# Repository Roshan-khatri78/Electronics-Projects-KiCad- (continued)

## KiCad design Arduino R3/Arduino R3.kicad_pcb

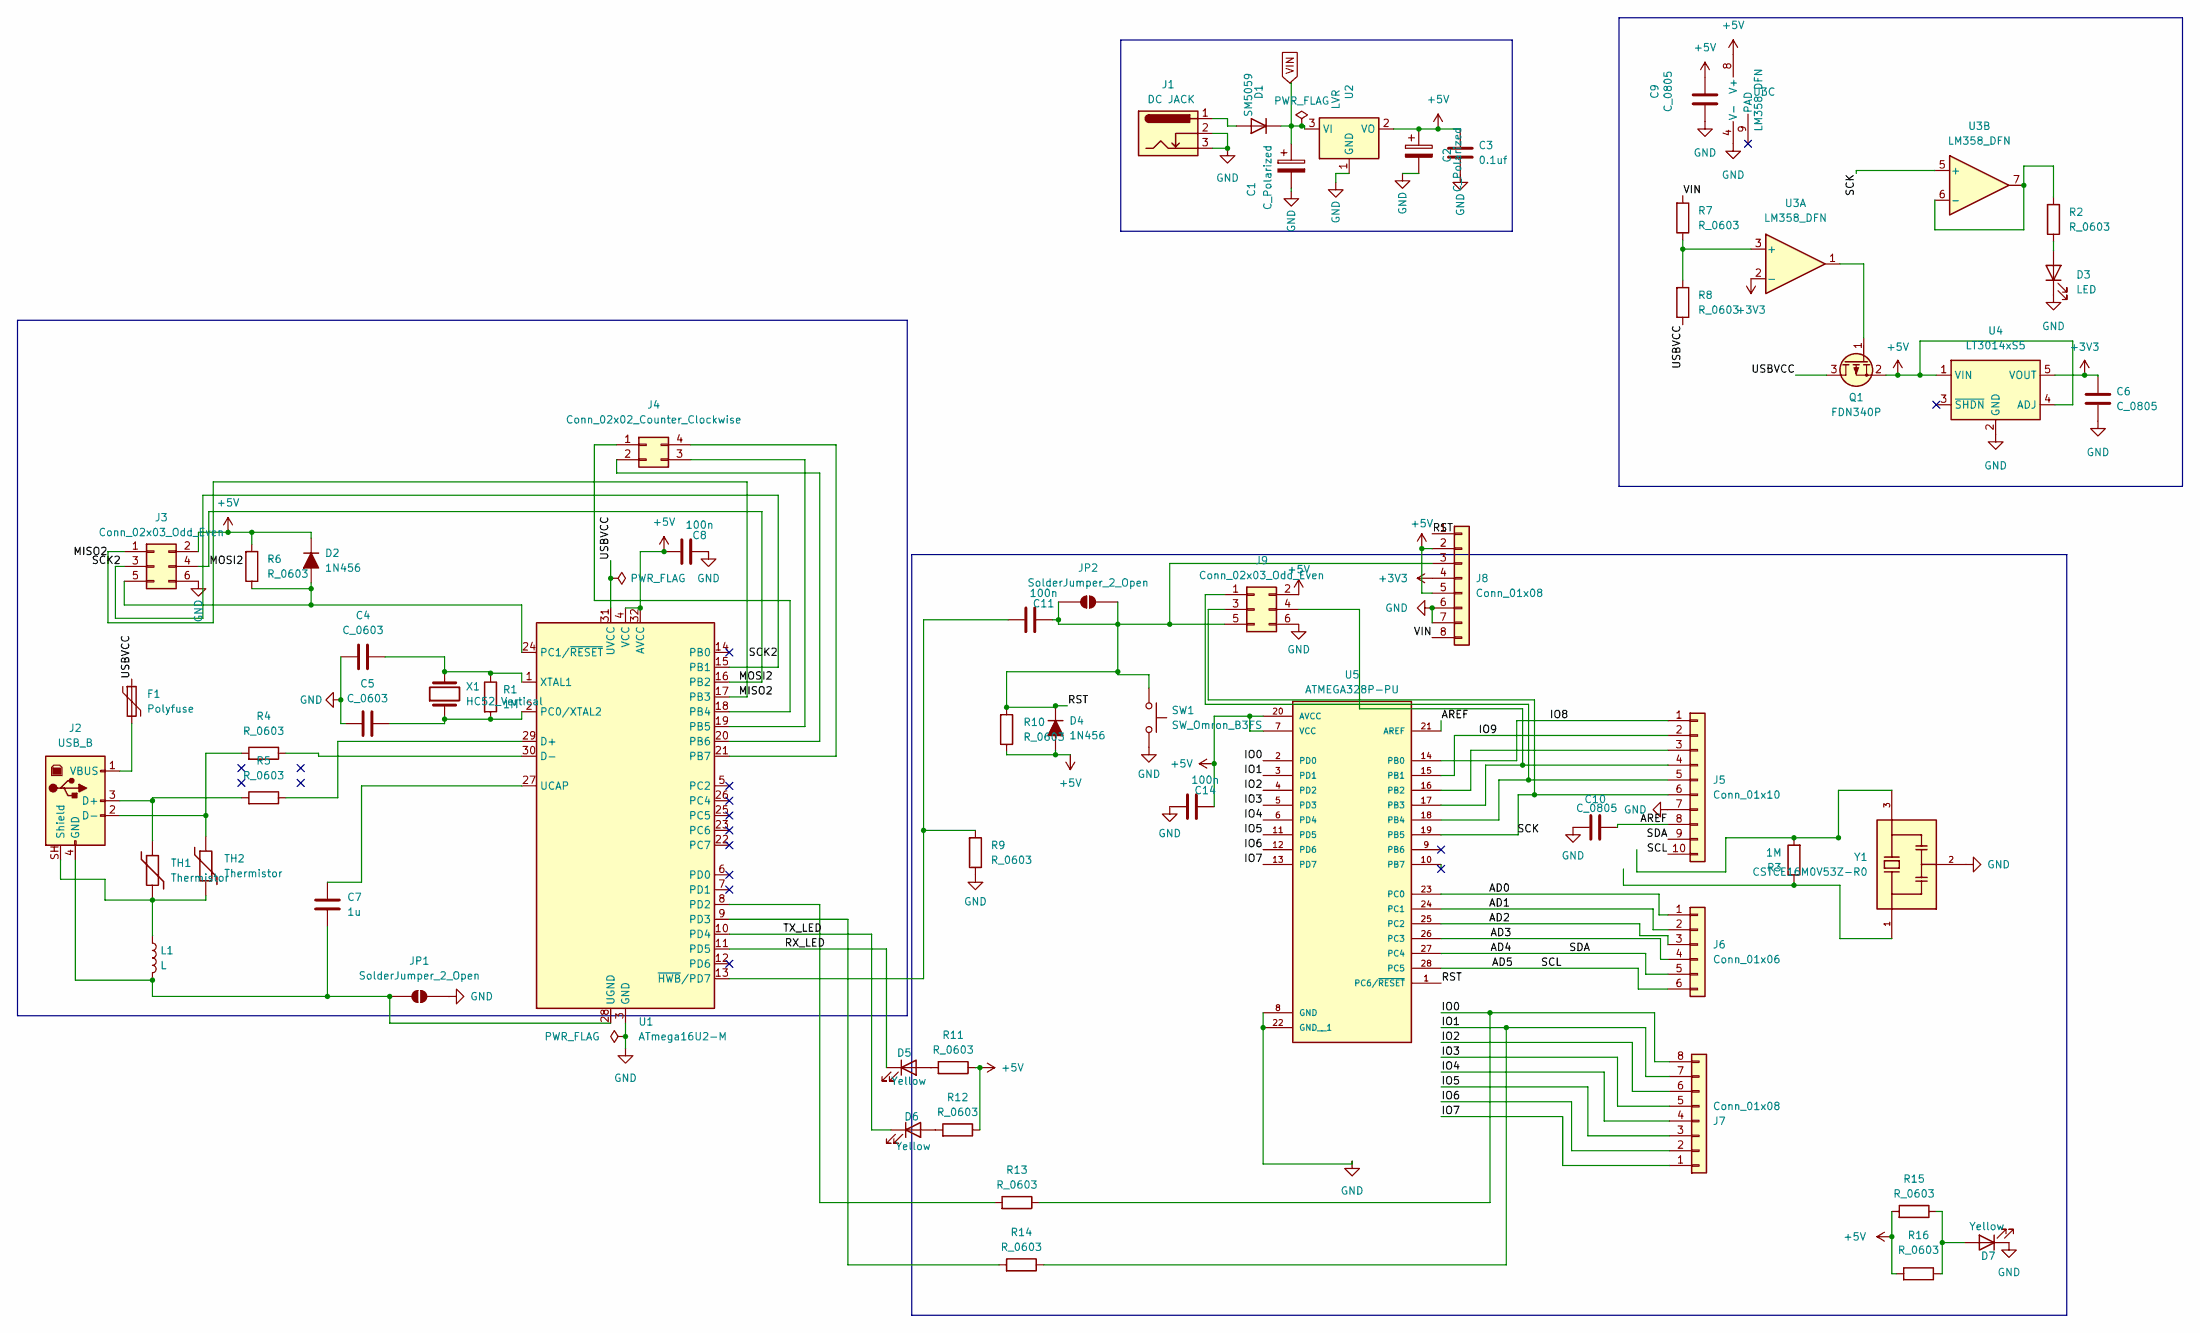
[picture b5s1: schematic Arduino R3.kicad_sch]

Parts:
C1, C2: C_Polarized; CP_Elec_8x5.4
C3: 0.1uf; C_0805_2012Metric
C4, C5: C_0603; C_0603_1608Metric
C6, C9, C10: C_0805; C_0805_2012Metric
C7: 1u; C_0603_1608Metric
C8, C11, C14: 100n; C_0603_1608Metric
D1: SM5059; D_MELF
D2, D4: 1N456; D_1206_3216Metric
D3: LED; LED_0805_2012Metric
D5, D6, D7: Yellow; LED_0805_2012Metric
F1: Polyfuse; Fuse_1812_4532Metric_Castellated
J1: DC JACK; BarrelJack_Kycon_KLDX-0202-xC_Horizontal
J2: USB_B; USB_B_Lumberg_2411_02_Horizontal
J3, J9: Conn_02x03_Odd_Even; PinHeader_2x03_P2.54mm_Vertical
J4: Conn_02x02_Counter_Clockwise; Wuerth_WR-PHD_610004243021_SMD_2x02_P2.54mm_Vertical
J5: Conn_01x10; PinSocket_1x10_P2.54mm_Vertical
J6: Conn_01x06; PinSocket_1x06_P2.54mm_Vertical
J7, J8: Conn_01x08; PinSocket_1x08_P2.54mm_Vertical
JP1, JP2: SolderJumper_2_Open; SolderJumper-2_P1.3mm_Open_RoundedPad1.0x1.5mm
L1: L; L_0201_0603Metric
Q1: FDN340P; SuperSOT-3
R1, R3: 1M; R_0805_2012Metric
R2, R4, R5, R6, R7, R8, R9, R10, R11, R12, R13, R14, R15, R16: R_0603; R_0603_1608Metric
SW1: SW_Omron_B3FS; SW_SPST_Omron_B3FS-100xP
TH1, TH2: Thermistor; R_0201_0603Metric
U1: ATmega16U2-M; QFN-32-1EP_5x5mm_P0.5mm_EP3.1x3.1mm
U2: LVR; SOT-223-3_TabPin2
U3: LM358_DFN; DFN-8-1EP_2x2mm_P0.5mm_EP1.05x1.75mm
U4: LT3014xS5; SOT-23-5
U5: ATMEGA328P-PU; DIP794W46P254L2967H457Q28B
X1: HC52_Vertical; Crystal_HC52-U_Vertical
Y1: CSTCE16M0V53Z-R0; OSC_CSTCE16M0V53Z-R0; PARTREV May 7, 2019

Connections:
+3V3: C6.1, J8.4, U3.2 (-), U4.5 (VOUT)
+5V: C2.1, C3.1, C8.1, C9.1, C14.2, D2.1 (K), D4.2 (A), J3.2, J8.2, J8.5, J9.2, Q1.2 (S), R6.1, R10.2, R11.2, R12.2, R15.1, R16.1, U1.4 (VCC), U1.32 (AVCC), U2.2 (VO), U3.8 (V+), U4.1 (VIN), U4.4 (ADJ), U5.7 (VCC), U5.20 (AVCC)
/AD0: J6.1, U5.23 (PC0)
/AD1: J6.2, U5.24 (PC1)
/AD2: J6.3, U5.25 (PC2)
/AD3: J6.4, U5.26 (PC3)
/AD4: J5.9, J6.5, U5.27 (PC4)
/AD5: J5.10, J6.6, U5.28 (PC5)
/AREF: C10.2, J5.8, U5.21 (AREF)
/IO0: J7.8, R13.2, U5.2 (PD0)
/IO1: J7.7, R14.2, U5.3 (PD1)
/IO2: J7.6, U5.4 (PD2)
/IO3: J7.5, U5.5 (PD3)
/IO4: J7.4, U5.6 (PD4)
/IO5: J7.3, U5.11 (PD5)
/IO6: J7.2, U5.12 (PD6)
/IO7: J7.1, U5.13 (PD7)
/IO8: J5.1, U5.14 (PB0)
/IO9: J5.2, U5.15 (PB1)
/MISO2: J3.1, U1.17 (PB3)
/MOSI2: J3.4, U1.16 (PB2)
/RST: D4.1 (K), J8.1, R10.1, SW1.1, U5.1 (PC6/~RESET)
/RX_LED: D5.1 (K), U1.11 (PD5)
/SCK: J5.6, J9.3, U3.5 (+), U5.19 (PB5)
/SCK2: J3.3, U1.15 (PB1)
/TX_LED: D6.1 (K), U1.10 (PD4)
/USBVCC: F1.1, Q1.3 (D), R8.2, U1.31 (UVCC)
GND: C1.2, C2.2, C3.2, C4.1, C5.1, C6.2, C8.2, C9.2, C10.1, C14.1, D3.1 (K), D7.1 (K), J1.2, J1.3, J3.6, J5.7, J8.6, J8.7, J9.6, JP1.2 (B), R9.2, SW1.2, U1.3 (GND), U1.33 (GND), U2.1 (GND), U3.4 (V-), U4.2 (GND), U5.8 (GND), U5.22 (GND__1), Y1.2; also elsewhere on the board
unnamed: D1.2 (A), J1.1
unnamed: D2.2 (A), J3.5, R6.2, U1.24 (PC1/~RESET)
unnamed: D3.2 (A), R2.2
unnamed: D5.2 (A), R11.1
unnamed: D6.2 (A), R12.1
unnamed: D7.2 (A), R15.2, R16.2
unnamed: J2.3 (D+), R5.1, TH1.1
unnamed: J2.2 (D-), R4.1, TH2.1
unnamed: C7.1, J2.4 (GND), JP1.1 (A), L1.2, U1.28 (UGND)
unnamed: J2.SH (Shield), L1.1, TH1.2, TH2.2
unnamed: F1.2, J2.1 (VBUS)
unnamed: J4.1, U1.18 (PB4)
unnamed: J4.2, U1.20 (PB6)
unnamed: J4.3, U1.19 (PB5)
unnamed: J4.4, U1.21 (PB7)
unnamed: J5.3, U5.16 (PB2)
unnamed: J5.4, J9.4, U5.17 (PB3)
unnamed: J5.5, J9.1, U5.18 (PB4)
unnamed: C11.2, J8.3, J9.5, JP2.1 (A), JP2.2 (B)
unnamed: Q1.1 (G), U3.1
unnamed: R3.1, Y1.1
unnamed: R3.2, Y1.3
unnamed: R5.2, U1.29 (D+)
unnamed: R4.2, U1.30 (D-)
unnamed: C5.2, R1.2, U1.2 (PC0/XTAL2), X1.1
unnamed: R13.1, U1.8 (PD2)
unnamed: R14.1, U1.9 (PD3)
unnamed: C7.2, U1.27 (UCAP)
unnamed: C4.2, R1.1, U1.1 (XTAL1), X1.2
unnamed: C11.1, R9.1, U1.13 (~HWB/PD7)
unnamed: R7.2, R8.1, U3.3 (+)
unnamed: R2.1, U3.6 (-), U3.7
VIN: C1.1, D1.1 (K), J8.8, R7.1, U2.3 (VI)

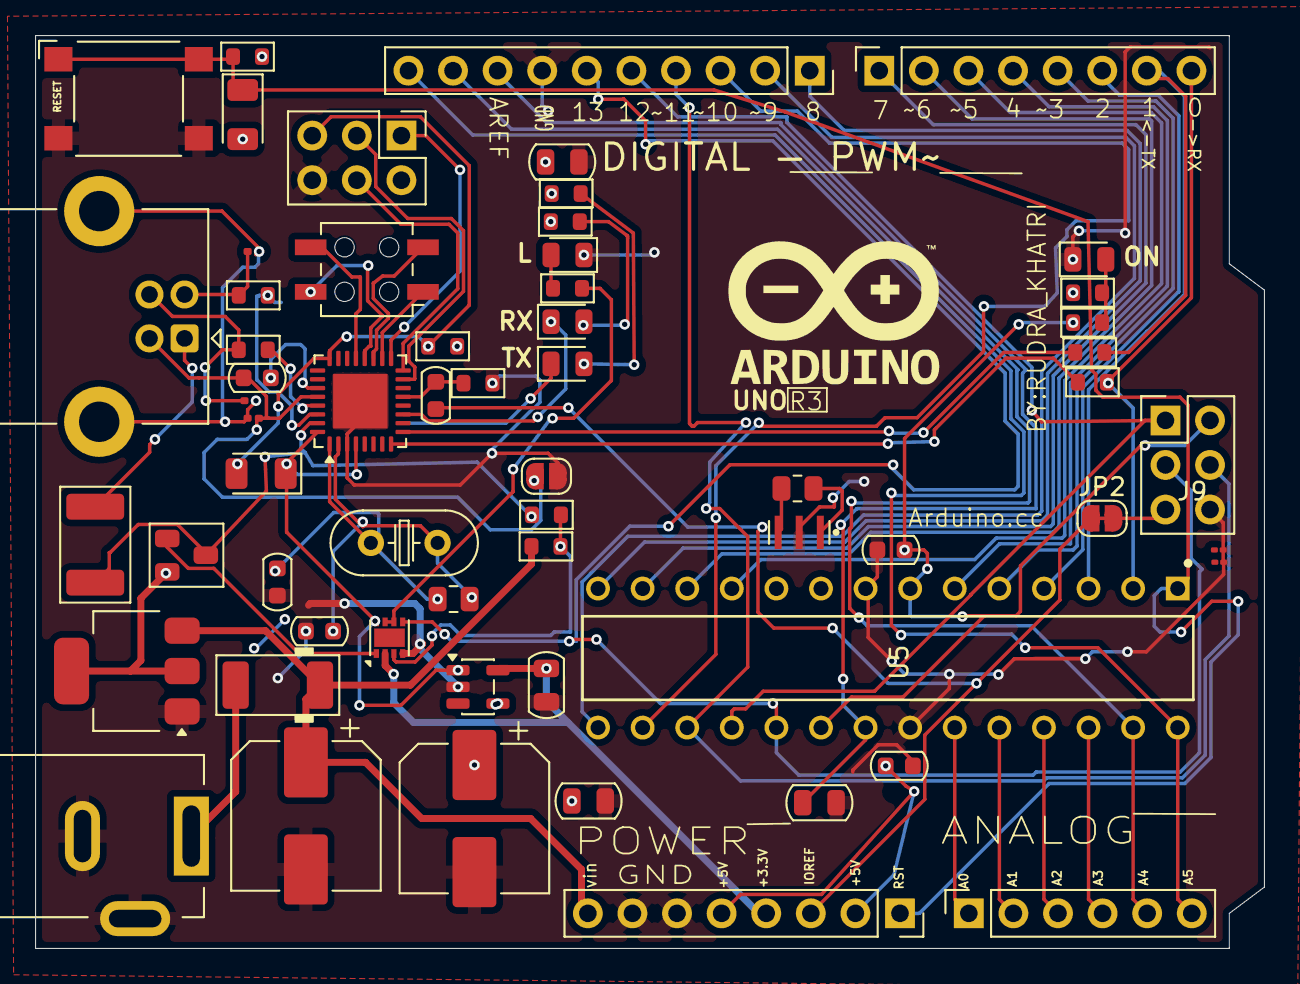
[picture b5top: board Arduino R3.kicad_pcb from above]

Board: 4 copper layers, 70.0 x 52.0 mm, 61 parts (0 on the bottom side), 61 nets.

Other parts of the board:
C12, C13: C_0603; C_01005_0402Metric

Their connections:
GND: C12.1, C13.1; also elsewhere on the board

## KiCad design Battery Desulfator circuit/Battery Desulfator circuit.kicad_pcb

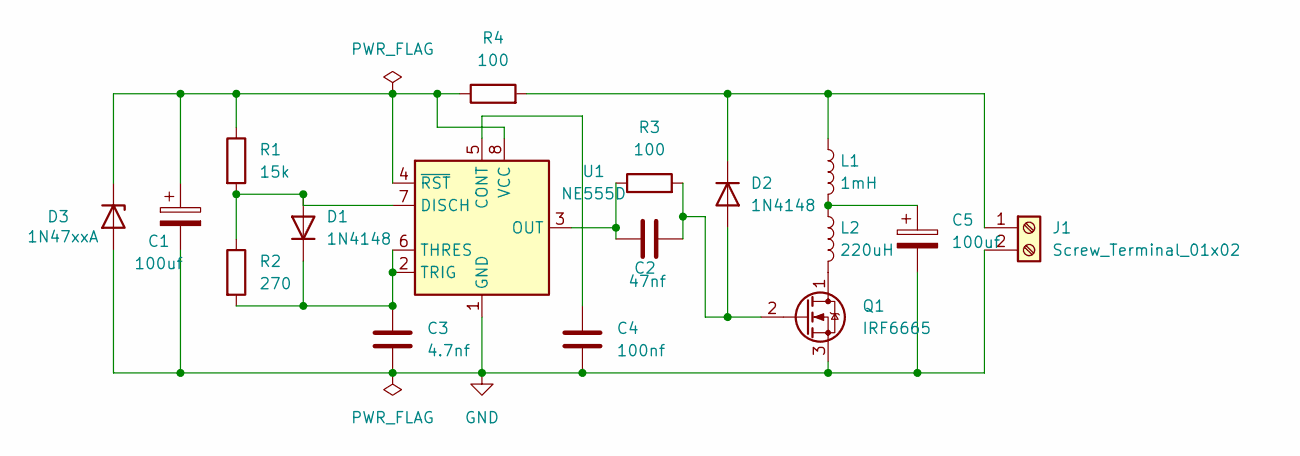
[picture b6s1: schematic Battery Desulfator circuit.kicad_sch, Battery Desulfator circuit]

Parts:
C1, C5: 100uf; CP_Axial_L10.0mm_D4.5mm_P15.00mm_Horizontal
C2: 47nf; CP_Axial_L10.0mm_D4.5mm_P15.00mm_Horizontal
C3: 4.7nf; CP_Axial_L10.0mm_D4.5mm_P15.00mm_Horizontal
C4: 100nf; CP_Axial_L10.0mm_D4.5mm_P15.00mm_Horizontal
D1, D2: 1N4148; D_DO-35_SOD27_P7.62mm_Horizontal
D3: 1N47xxA; D_DO-41_SOD81_P10.16mm_Horizontal
J1: Screw_Terminal_01x02; TerminalBlock_Phoenix_MKDS-1,5-2_1x02_P5.00mm_Horizontal
L1: 1mH; Choke_EPCOS_B82722A
L2: 220uH; Choke_EPCOS_B82722A
Q1: IRF6665; DirectFET_SH
R1: 15k; R_Axial_DIN0204_L3.6mm_D1.6mm_P1.90mm_Vertical
R2: 270; R_Axial_DIN0204_L3.6mm_D1.6mm_P1.90mm_Vertical
R3, R4: 100; R_Axial_DIN0204_L3.6mm_D1.6mm_P1.90mm_Vertical
U1: NE555D; SOIC-8_3.9x4.9mm_P1.27mm

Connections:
GND: C1.2, C3.2, C4.2, C5.2, D3.2 (A), J1.2, Q1.3 (S), U1.1 (GND); also elsewhere on the board
unnamed: C5.1, L1.2, L2.1
unnamed: D1.2 (A), R1.2, R2.1, U1.7 (DISCH)
unnamed: C3.1, D1.1 (K), R2.2, U1.2 (TRIG), U1.6 (THRES)
unnamed: C2.2, D2.2 (A), Q1.2 (G), R3.2
unnamed 5: D2.1 (K), J1.1, L1.1, R4.2; also elsewhere on the board
unnamed: C1.1, D3.1 (K), R1.1, R4.1, U1.4 (~RST), U1.8 (VCC)
unnamed: L2.2, Q1.1 (D)
unnamed: C4.1, U1.5 (CONT)
unnamed: C2.1, R3.1, U1.3 (OUT)

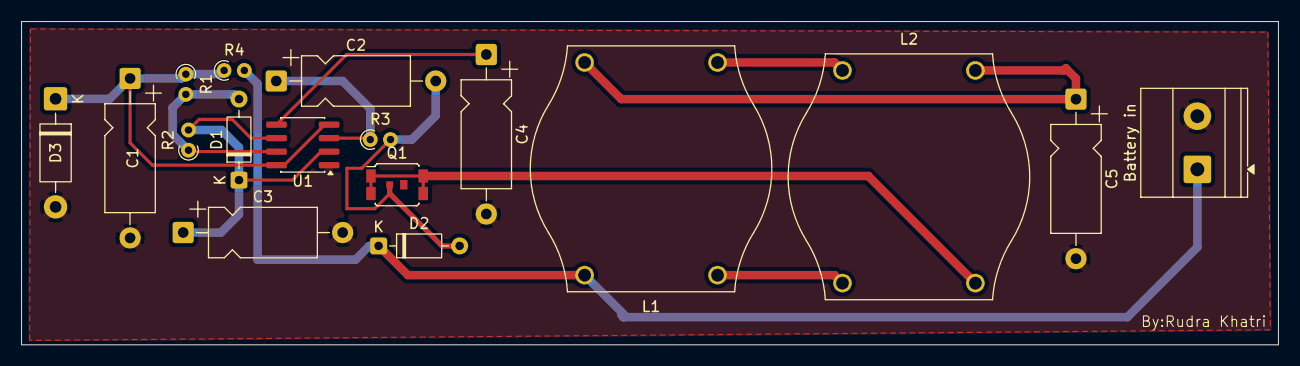
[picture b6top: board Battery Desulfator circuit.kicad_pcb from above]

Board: 2 copper layers, 118.2 x 30.4 mm, 17 parts (0 on the bottom side), 10 nets.

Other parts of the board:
Battery in: Screw_Terminal_01x02; TerminalBlock_Phoenix_MKDS-1,5-2_1x02_P5.00mm_Horizontal

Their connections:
GND: Battery in.2; also elsewhere on the board
unnamed 5: Battery in.1; also elsewhere on the board

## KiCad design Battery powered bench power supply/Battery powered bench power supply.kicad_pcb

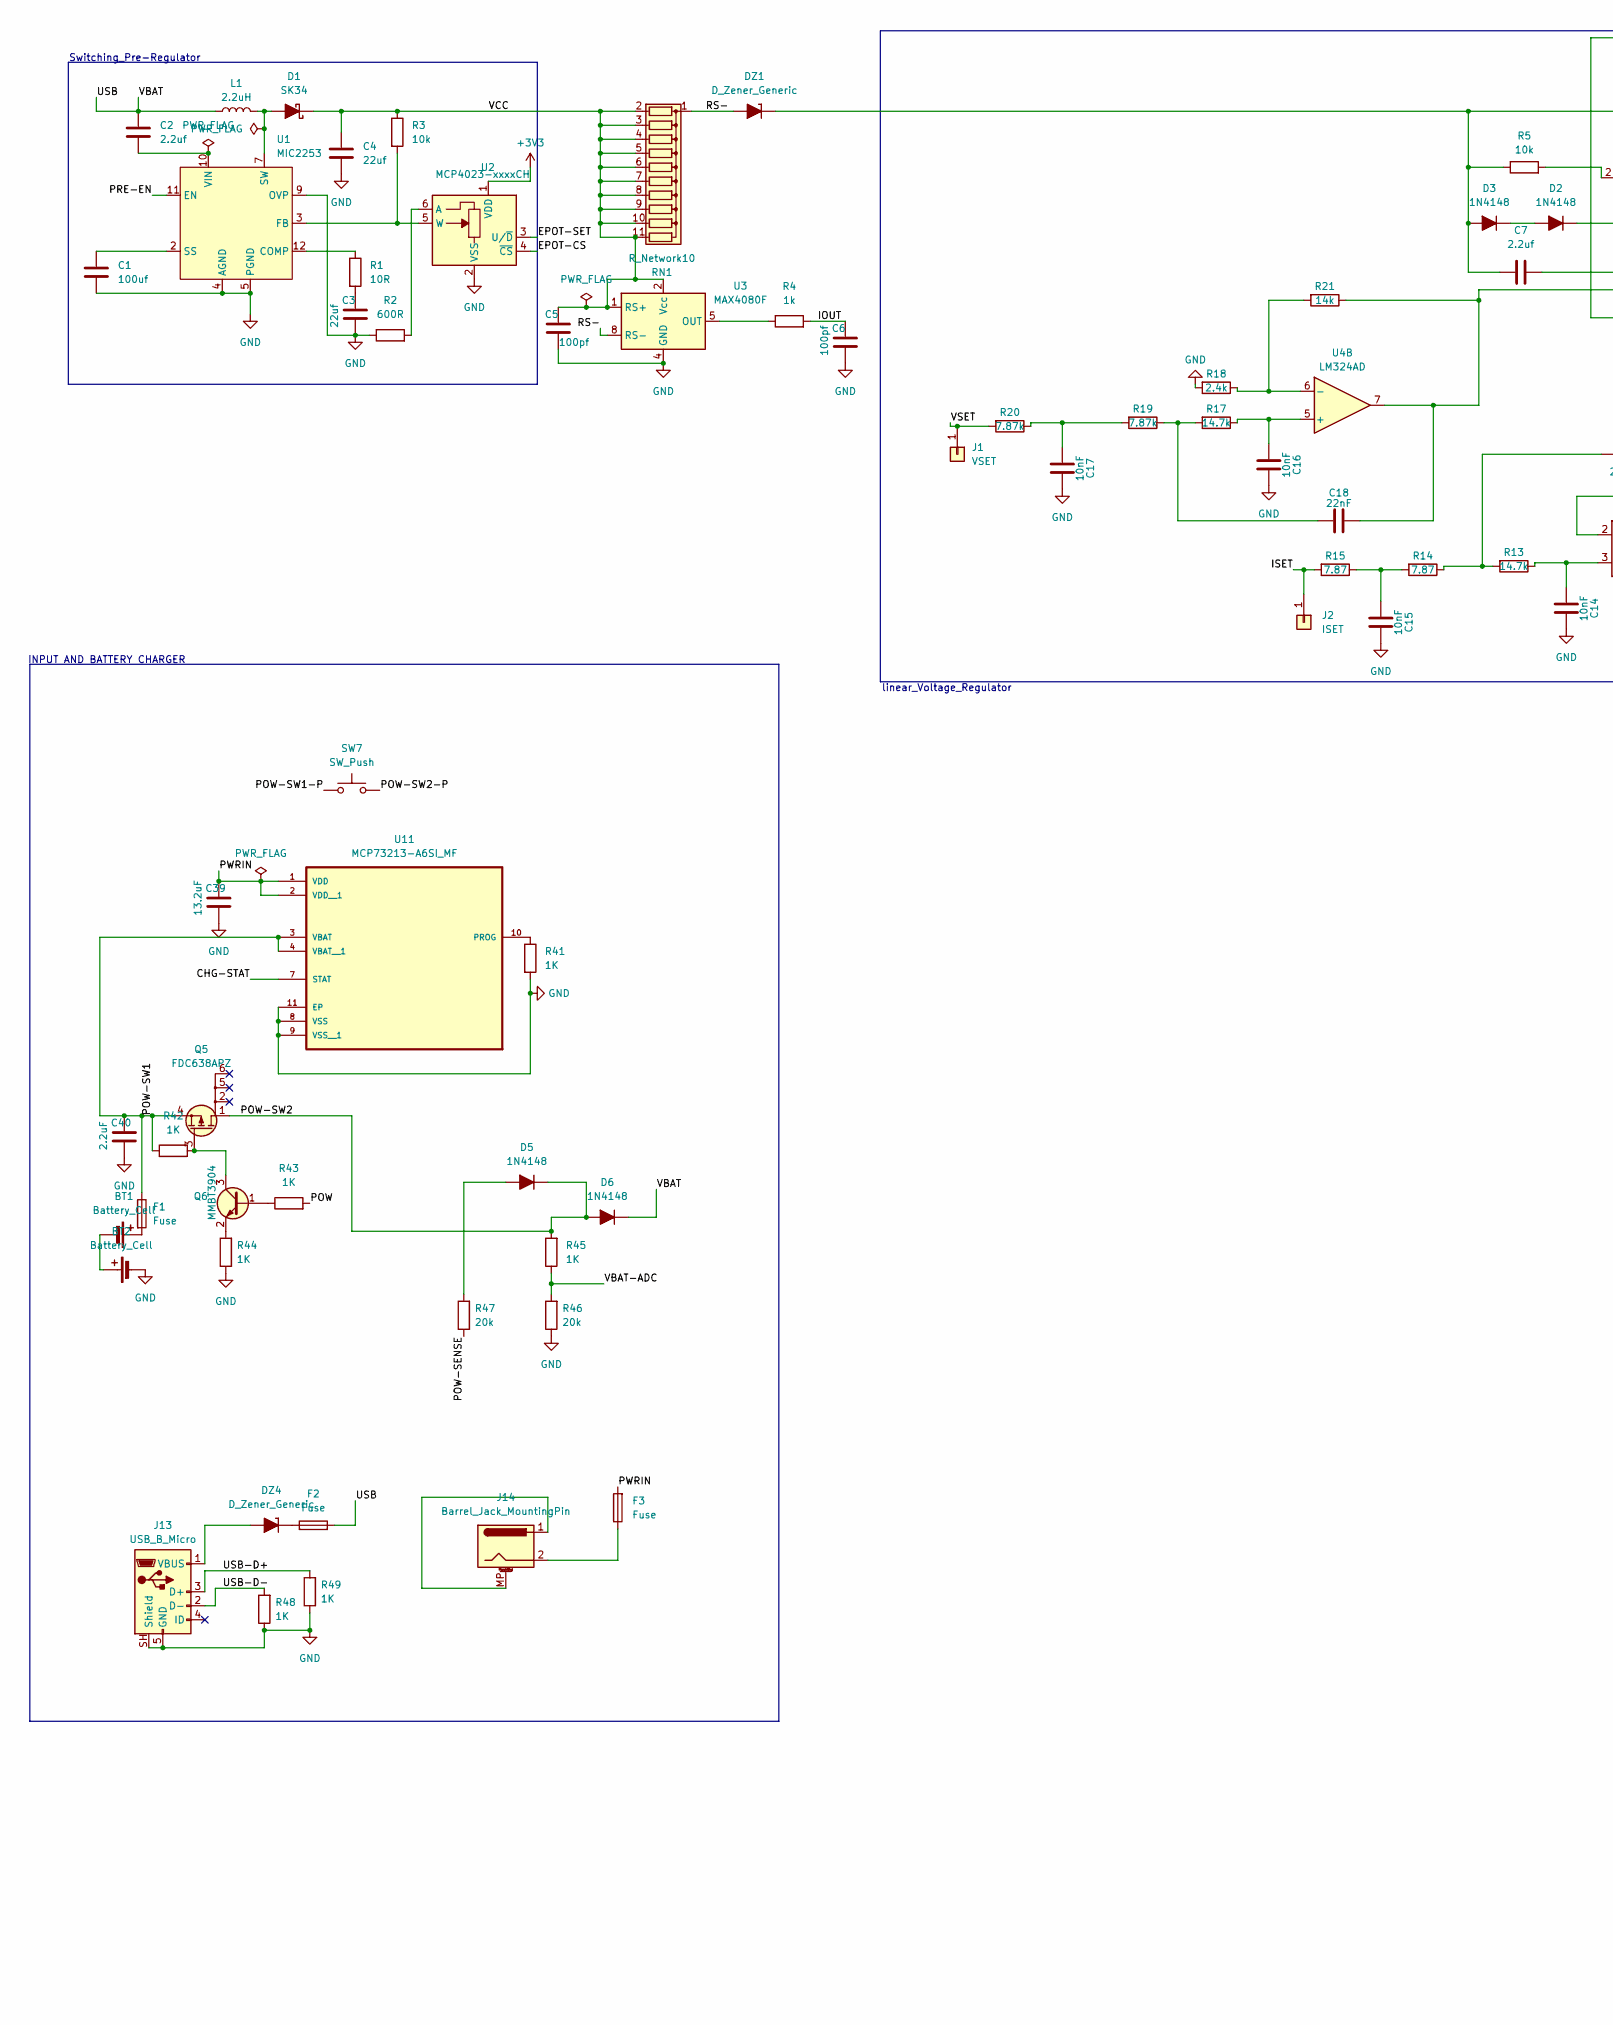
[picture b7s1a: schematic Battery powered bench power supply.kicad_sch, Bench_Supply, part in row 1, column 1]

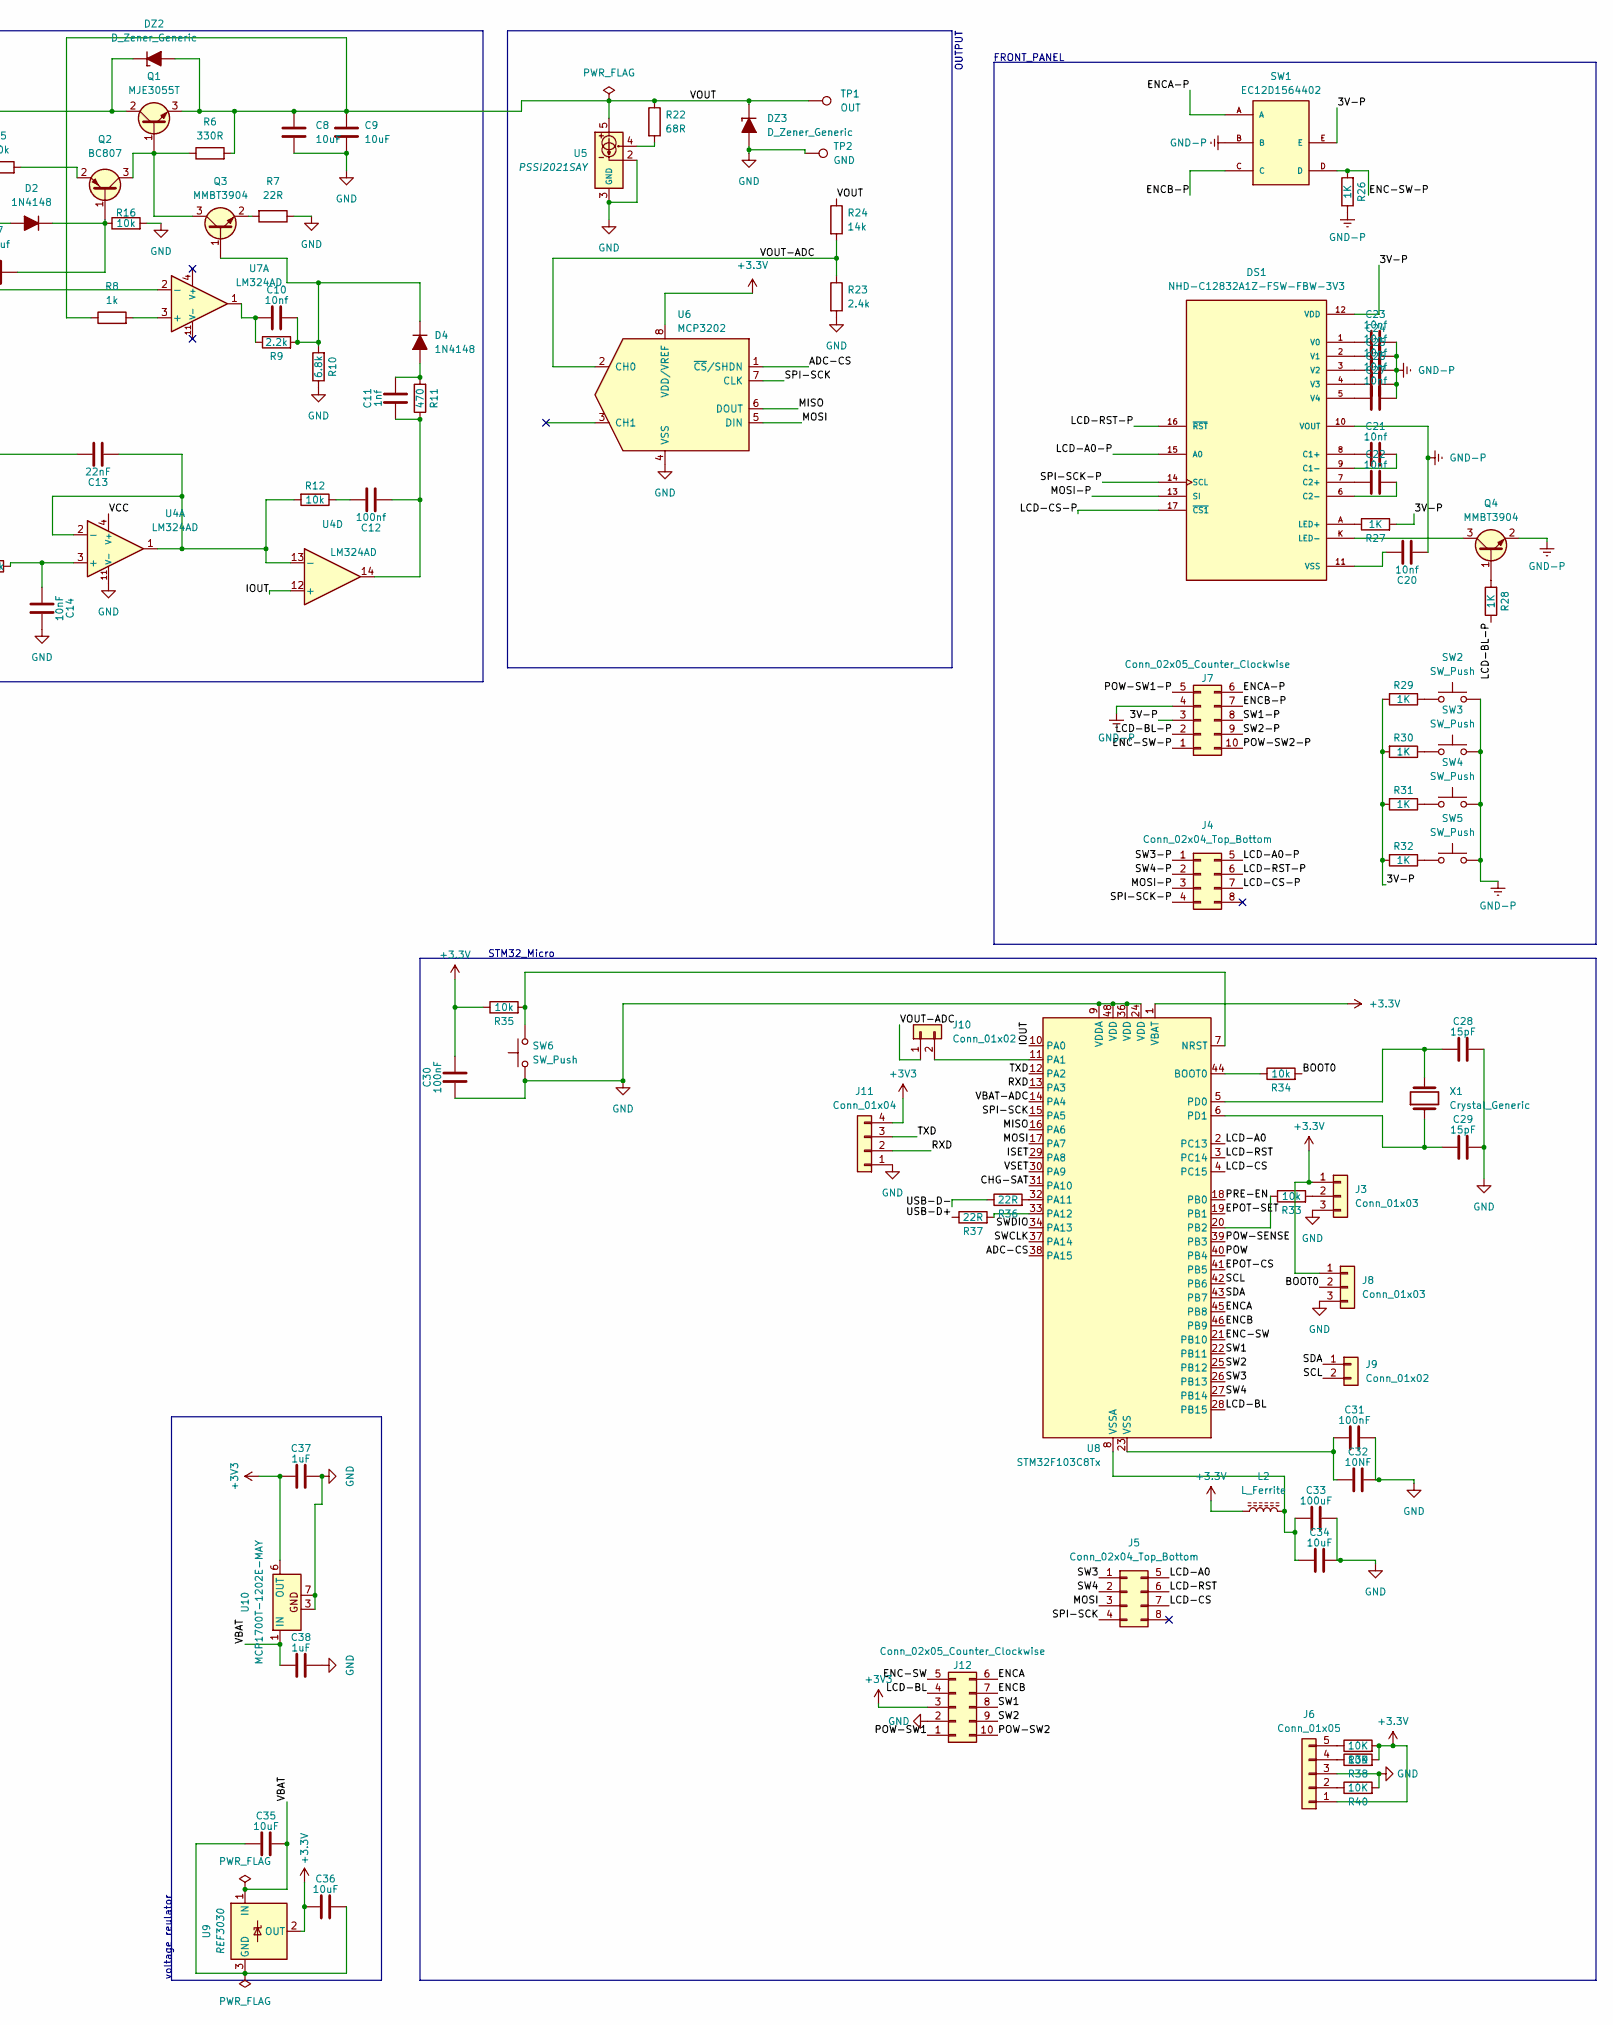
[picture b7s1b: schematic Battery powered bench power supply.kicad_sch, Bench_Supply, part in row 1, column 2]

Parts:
BT1, BT2: Battery_Cell; BatteryHolder_Keystone_2460_1xAA
C1: 100uf; C_1206_3216Metric_Pad1.33x1.80mm_HandSolder
C2, C7: 2.2uf; C_1206_3216Metric_Pad1.33x1.80mm_HandSolder
C3, C4: 22uf; C_1206_3216Metric_Pad1.33x1.80mm_HandSolder
C5, C6: 100pf; C_1206_3216Metric_Pad1.33x1.80mm_HandSolder
C8, C9, C34, C35, C36: 10uF; C_1206_3216Metric_Pad1.33x1.80mm_HandSolder
C10, C20, C21, C22, C23, C24, C25, C26, C27: 10nf; C_1206_3216Metric_Pad1.33x1.80mm_HandSolder
C11: 1nf; C_1206_3216Metric_Pad1.33x1.80mm_HandSolder
C12: 100nf; C_1206_3216Metric_Pad1.33x1.80mm_HandSolder
C13, C18: 22nF; C_1206_3216Metric_Pad1.33x1.80mm_HandSolder
C14, C15, C16, C17: 10nF; C_1206_3216Metric_Pad1.33x1.80mm_HandSolder
C28, C29: 15pF; C_1206_3216Metric_Pad1.33x1.80mm_HandSolder
C30, C31: 100nF; C_1206_3216Metric_Pad1.33x1.80mm_HandSolder
C32: 10NF; C_1206_3216Metric_Pad1.33x1.80mm_HandSolder
C33: 100uF; C_1206_3216Metric_Pad1.33x1.80mm_HandSolder
C37, C38: 1uF; C_1206_3216Metric_Pad1.33x1.80mm_HandSolder
C39: 13.2uF; C_1206_3216Metric_Pad1.33x1.80mm_HandSolder
C40: 2.2uF; C_1206_3216Metric_Pad1.33x1.80mm_HandSolder
D1: SK34; D_SMC
D2, D3, D4, D5, D6: 1N4148; D_DO-35_SOD27_P7.62mm_Horizontal
DS1: NHD-C12832A1Z-FSW-FBW-3V3; LCD_NHD-C12832A1Z-FSW-FBW-3V3; PARTREV 7
DZ1, DZ2, DZ3: D_Zener_Generic; D_1206_3216Metric_Pad1.42x1.75mm_HandSolder
DZ4: D_Zener_Generic; D_1210_3225Metric
F1, F2, F3: Fuse; Fuse_1210_3225Metric_Pad1.42x2.65mm_HandSolder
J1: VSET; PinHeader_1x01_P1.00mm_Vertical
J2: ISET; PinHeader_1x01_P1.00mm_Vertical
J3, J8: Conn_01x03; FanPinHeader_1x03_P2.54mm_Vertical
J4, J5: Conn_02x04_Top_Bottom; Harwin_LTek-Male_2x04_P2.00mm_Vertical
J6: Conn_01x05; PinHeader_1x05_P1.00mm_Vertical
J7, J12: Conn_02x05_Counter_Clockwise; Tag-Connect_TC2050-IDC-NL_2x05_P1.27mm_Vertical
J9, J10: Conn_01x02; PinHeader_1x02_P1.00mm_Vertical
J11: Conn_01x04; FanPinHeader_1x04_P2.54mm_Vertical
J13: USB_B_Micro; USB_Mini-B_Lumberg_2486_01_Horizontal
J14: Barrel_Jack_MountingPin; BarrelJack_Horizontal
L1: 2.2uH; L_1206_3216Metric_Pad1.22x1.90mm_HandSolder
L2: L_Ferrite; L_Ferrocore_DLG-0302
Q1: MJE3055T; TO-220-3_Vertical_BCE
Q2: BC807; SOT-23
Q3, Q4, Q6: MMBT3904; SOT-23
Q5: FDC638APZ; SuperSOT-6
R1: 10R; R_0815_2038Metric_Pad1.20x4.05mm_HandSolder
R2: 600R; R_0815_2038Metric_Pad1.20x4.05mm_HandSolder
R3, R5, R12, R16, R33, R34, R35: 10k; R_0815_2038Metric_Pad1.20x4.05mm_HandSolder
R4, R8: 1k; R_0815_2038Metric_Pad1.20x4.05mm_HandSolder
R6: 330R; R_0815_2038Metric_Pad1.20x4.05mm_HandSolder
R7, R36, R37: 22R; R_0815_2038Metric_Pad1.20x4.05mm_HandSolder
R9: 2.2k; R_0815_2038Metric_Pad1.20x4.05mm_HandSolder
R10: 6.8k; R_0815_2038Metric_Pad1.20x4.05mm_HandSolder
R11: 470; R_0815_2038Metric_Pad1.20x4.05mm_HandSolder
R13, R17: 14.7k; R_0815_2038Metric_Pad1.20x4.05mm_HandSolder
R14, R15: 7.87; R_0815_2038Metric_Pad1.20x4.05mm_HandSolder
R18, R23: 2.4k; R_0815_2038Metric_Pad1.20x4.05mm_HandSolder
R19, R20: 7.87k; R_0815_2038Metric_Pad1.20x4.05mm_HandSolder
R21, R24: 14k; R_0815_2038Metric_Pad1.20x4.05mm_HandSolder
R22: 68R; R_0815_2038Metric_Pad1.20x4.05mm_HandSolder
R26, R27, R28, R29, R30, R31, R32, R41, R42, R43, R44, R45, R48, R49: 1K; R_0815_2038Metric_Pad1.20x4.05mm_HandSolder
R38, R39, R40: 10K; R_0815_2038Metric_Pad1.20x4.05mm_HandSolder
R46, R47: 20k; R_0815_2038Metric_Pad1.20x4.05mm_HandSolder
RN1: R_Network10; R_Array_SIP11
SW1: EC12D1564402; EC12D; FARNELL 2065075
SW2, SW3, SW4, SW5, SW6, SW7: SW_Push; SW_PUSH_6mm
TP1: OUT; TestPoint_Pad_1.0x1.0mm
TP2: GND; TestPoint_Pad_1.0x1.0mm
U1: MIC2253; DFN-12-1EP_3x3mm_P0.5mm_EP1.6x2.5mm_ThermalVias
U2: MCP4023-xxxxCH; SOT-23-6
U3: MAX4080F; SOIC-8_3.9x4.9mm_P1.27mm
U4, U7: LM324AD; SOIC-14_3.9x8.7mm_P1.27mm
U5: PSSI2021SAY; SOT-353_SC-70-5
U6: MCP3202; SON50P300X300X100-11N
U8: STM32F103C8Tx; LQFP-48_7x7mm_P0.5mm
U9: REF3030; SOT-23
U10: MCP1700T-1202E-MAY; DFN-6-1EP_2x2mm_P0.65mm_EP1x1.6mm
U11: MCP73213-A6SI_MF; SON50P300X300X100-11N
X1: Crystal_Generic; Crystal_HC18-U_Vertical

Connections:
+3.3V: C30.1, C36.2, J3.1, J6.1, J8.1, L2.1, R35.1, R38.2, R39.2, U6.8 (VDD/VREF), U8.1 (VBAT), U9.2 (OUT)
+3V3: C37.2, J11.4, J12.3, U2.1 (VDD), U10.6 (OUT)
/3V-P: DS1.12 (VDD), J7.3, R27.2, R29.2, R30.2, R31.2, R32.2, SW1.E
/ADC-CS: U6.1 (~CS/SHDN), U8.38 (PA15)
/BOOT0: J8.2, R34.2
/CHG-SAT: U8.31 (PA10)
/CHG-STAT: U11.7 (STAT)
/ENC-SW: J12.5, U8.21 (PB10)
/ENC-SW-P: J7.1, R26.2, SW1.D
/ENCA: J12.6, U8.45 (PB8)
/ENCA-P: J7.6, SW1.A
/ENCB: J12.7, U8.46 (PB9)
/ENCB-P: J7.7, SW1.C
/EPOT-CS: U2.4 (~CS), U8.41 (PB5)
/EPOT-SET: U2.3 (U/~D), U8.19 (PB1)
/IOUT: C6.1, R4.2, U4.12 (+), U8.10 (PA0)
/ISET: J2.1 (Pin_1_1), R15.2, U8.29 (PA8)
/LCD-A0: J5.5, U8.2 (PC13)
/LCD-A0-P: DS1.15 (A0), J4.5
/LCD-BL: J12.4, U8.28 (PB15)
/LCD-BL-P: J7.2, R28.1
/LCD-CS: J5.7, U8.4 (PC15)
/LCD-CS-P: DS1.17 (~CS1), J4.7
/LCD-RST: J5.6, U8.3 (PC14)
/LCD-RST-P: DS1.16 (~RST), J4.6
/MISO: U6.6 (DOUT), U8.16 (PA6)
/MOSI: J5.3, U6.5 (DIN), U8.17 (PA7)
/MOSI-P: DS1.13 (SI), J4.3
/POW: R43.2, U8.40 (PB4)
/POW-SENSE: R47.1, U8.39 (PB3)
/POW-SW1: C40.1, F1.1, J12.1, Q5.4 (S), R42.1, U11.3 (VBAT), U11.4 (VBAT__1)
/POW-SW1-P: J7.5, SW7.1
/POW-SW2: D5.1 (K), D6.2 (A), J12.10, Q5.1 (D), R45.2
/POW-SW2-P: J7.10, SW7.2
/PRE-EN: U1.11 (EN), U8.18 (PB0)
/PWRIN: C39.1, F3.2, U11.1 (VDD), U11.2 (VDD__1)
/RS-: DZ1.2 (A), RN1.1 (common), U3.8 (RS-)
/RXD: J11.2, U8.13 (PA3)
/SCL: J9.2, U8.42 (PB6)
/SDA: J9.1, U8.43 (PB7)
/SPI-SCK: J5.4, U6.7 (CLK), U8.15 (PA5)
/SPI-SCK-P: DS1.14 (SCL), J4.4
/SW1: J12.8, U8.22 (PB11)
/SW1-P: J7.8
/SW2: J12.9, U8.25 (PB12)
/SW2-P: J7.9
/SW3: J5.1, U8.26 (PB13)
/SW3-P: J4.1
/SW4: J5.2, U8.27 (PB14)
/SW4-P: J4.2
/SWCLK: U8.37 (PA14)
/SWDIO: U8.34 (PA13)
/TXD: J11.3, U8.12 (PA2)
/USB: C2.1, C35.1, C38.2, D6.1 (K), F2.2, L1.1, U9.1 (IN), U10.1 (IN)
/USB-D+: J13.3 (D+), R37.1, R49.2
/USB-D-: J13.2 (D-), R36.1, R48.2
/VBAT-ADC: R45.1, R46.2, U8.14 (PA4)
/VCC: C4.1, C5.1, D1.1 (K), R3.1, RN1.2 (R1), RN1.3 (R2), RN1.4 (R3), RN1.5 (R4), RN1.6 (R5), RN1.7 (R6), RN1.8 (R7), RN1.9 (R8), RN1.10 (R9), RN1.11 (R10), U3.1 (RS+), U3.2 (Vcc), U4.4 (V+)
/VOUT: C8.2, C9.2, DZ2.2 (A), DZ3.1 (K), Q1.3 (E), R6.2, R8.1, R22.1, R24.1, TP1.1 (1_1), U5.5
/VOUT-ADC: J10.1, R23.1, R24.2, U6.2 (CH0)
/VSET: J1.1 (Pin_1_1), R20.2, U8.30 (PA9)
GND: BT2.2 (-), C1.2, C3.2, C4.2, C5.2, C6.2, C8.1, C9.1, C14.1, C15.1, C16.1, C17.1, C28.1, C29.1, C30.2, C31.1, C32.1, C33.1, C34.1, C37.1, C38.1, C39.2, C40.2, DZ3.2 (A), J3.3, J6.3, J8.3, J11.1, J12.2, J13.5 (GND), J13.SH (Shield), R2.1, R7.1, R10.1, R16.2, R18.2, R23.2, R40.2, R41.2, R44.1, R46.1, R48.1, R49.1, SW6.1, TP2.1 (1_1), U1.4 (AGND), U1.5 (PGND), U1.6 (PGND), U1.9 (OVP), U1.13 (PGND), U2.2 (VSS), U3.4 (GND), U4.11 (V-), U5.2, U5.3 (GND_3), U6.4 (VSS), U8.9 (VDDA), U8.24 (VDD), U8.36 (VDD), U8.48 (VDD), U10.3, U10.7, U11.8 (VSS), U11.9 (VSS__1), U11.11 (EP)
GND-P: C20.2, C23.1, C24.1, C25.1, C26.1, C27.1, DS1.10 (VOUT), J7.4, Q4.2 (E), R26.1, SW1.B, SW2.2, SW3.2, SW4.2, SW5.2
unnamed: BT1.1 (+), F1.2
unnamed: BT1.2 (-), BT2.1 (+)
unnamed: C3.1, R1.2
unnamed: C10.2, R9.1, U7.1
unnamed: C11.2, C12.2, R11.1, U4.14
unnamed: C12.1, R12.1
unnamed: C13.1, R13.2, R14.1
unnamed: C15.2, R14.2, R15.1
unnamed: C17.2, R19.2, R20.1
unnamed: C18.2, R17.2, R19.1
unnamed: C31.2, C32.2, U8.23 (VSS), U8.35 (VSS), U8.47 (VSS)
unnamed: D1.2 (A), L1.2, U1.7 (SW), U1.8 (SW)
unnamed: D2.2 (A), D3.1 (K)
unnamed: C7.2, D2.1 (K), Q2.1 (B), R16.1
unnamed: C7.1, D3.2 (A), DZ1.1 (K), DZ2.1 (K), Q1.2 (C), R5.1
unnamed: C11.1, D4.2 (A), R11.2
unnamed: C10.1, D4.1 (K), Q3.1 (B), R9.2, R10.2
unnamed: D5.2 (A), R47.2
unnamed: C21.2, DS1.8 (C1+)
unnamed: C21.1, DS1.9 (C1-)
unnamed: C22.2, DS1.7 (C2+)
unnamed: C22.1, DS1.6 (C2-)
unnamed: DS1.A (LED+), R27.1
unnamed: DS1.K (LED-), Q4.3 (C)
unnamed: C23.2, DS1.1 (V0)
unnamed: C24.2, DS1.2 (V1)
unnamed: C25.2, DS1.3 (V2)
unnamed: C26.2, DS1.4 (V3)
unnamed: C27.2, DS1.5 (V4)
unnamed: C20.1, DS1.11 (VSS)
unnamed: DZ4.2 (A), J13.1 (VBUS)
unnamed: DZ4.1 (K), F2.1
unnamed: F3.1, J14.2
unnamed: J3.2, R33.2
unnamed: J6.2, R40.1
unnamed: J6.4, R38.1
unnamed: J6.5, R39.1
unnamed: J10.2, U8.11 (PA1)
unnamed: J14.1, J14.MP (MountPin)
unnamed: Q1.1 (B), Q2.3 (C), Q3.3 (C), R6.1
unnamed: Q2.2 (E), R5.2
unnamed: Q3.2 (E), R7.2
unnamed: Q4.1 (B), R28.2
unnamed: Q5.3 (G), Q6.3 (C), R42.2
unnamed: Q6.1 (B), R43.1
unnamed: Q6.2 (E), R44.2
unnamed: R22.2, U5.4
unnamed: R29.1, SW2.1
unnamed: R30.1, SW3.1
unnamed: R31.1, SW4.1
unnamed: R32.1, SW5.1
unnamed: R1.1, U1.12 (COMP)
unnamed: R3.2, U1.3 (FB), U2.5 (W)
unnamed: C1.1, U1.2 (SS)
unnamed: C2.2, U1.10 (VIN)
unnamed: R2.2, U2.6 (A)
unnamed: R4.1, U3.5 (OUT)
unnamed: C14.2, R13.1, U4.3 (+)
unnamed: C13.2, R12.2, U4.1, U4.2 (-), U4.13 (-)
unnamed: C16.2, R17.1, U4.5 (+)
unnamed: R18.1, R21.2, U4.6 (-)
unnamed: R8.2, U7.3 (+)
unnamed: C18.1, R21.1, U4.7, U7.2 (-)
unnamed: R34.1, U8.44 (BOOT0)
unnamed: R35.2, SW6.2, U8.7 (NRST)
unnamed: R36.2, U8.32 (PA11)
unnamed: R37.2, U8.33 (PA12)
unnamed: R33.1, U8.20 (PB2)
unnamed: C28.2, U8.5 (PD0), X1.2
unnamed: C29.2, U8.6 (PD1), X1.1
unnamed: C33.2, C34.2, L2.2, U8.8 (VSSA)
unnamed: C35.2, C36.1, U9.3 (GND)
unnamed: R41.1, U11.10 (PROG)

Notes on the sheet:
INPUT AND BATTERY CHARGER
linear_Voltage_Regulator
STM32_Micro
Switching_Pre-Regulator
voltage reulator
FRONT_PANEL
OUTPUT

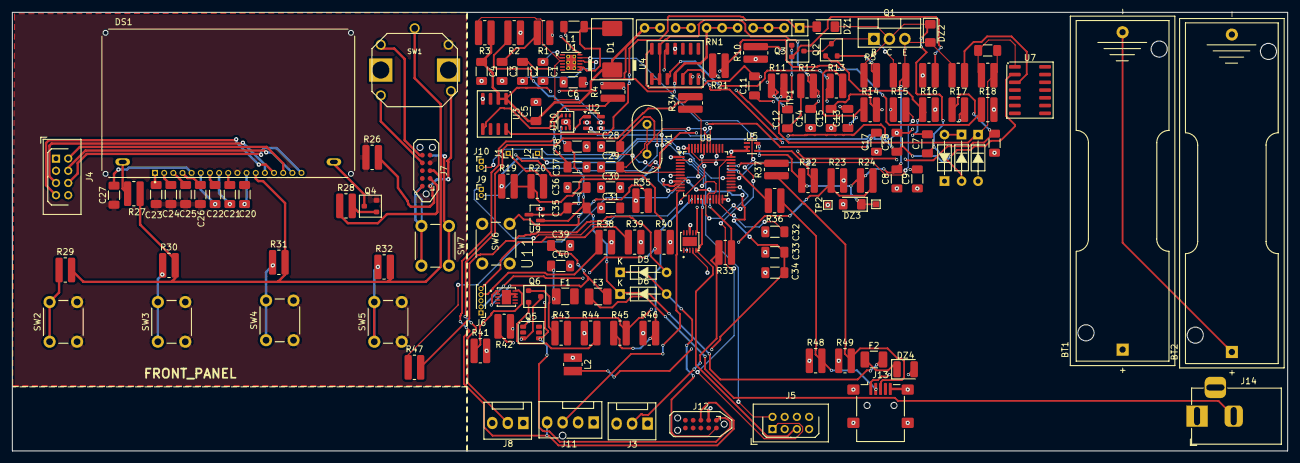
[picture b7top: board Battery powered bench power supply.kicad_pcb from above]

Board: 4 copper layers, 208.9 x 71.8 mm, 147 parts (0 on the bottom side), 127 nets.
